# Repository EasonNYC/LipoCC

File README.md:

# LipoCC
Author: Eason Smith (Eason@EasonRobotics.com)

A Coulomb Counter PCB for LiPo battery monitoring. Designed in Cadsoft Eagle.

Further details can be found at [http://www.easonrobotics.com/?portfolio=lipocc](http://www.easonrobotics.com/?portfolio=lipocc)

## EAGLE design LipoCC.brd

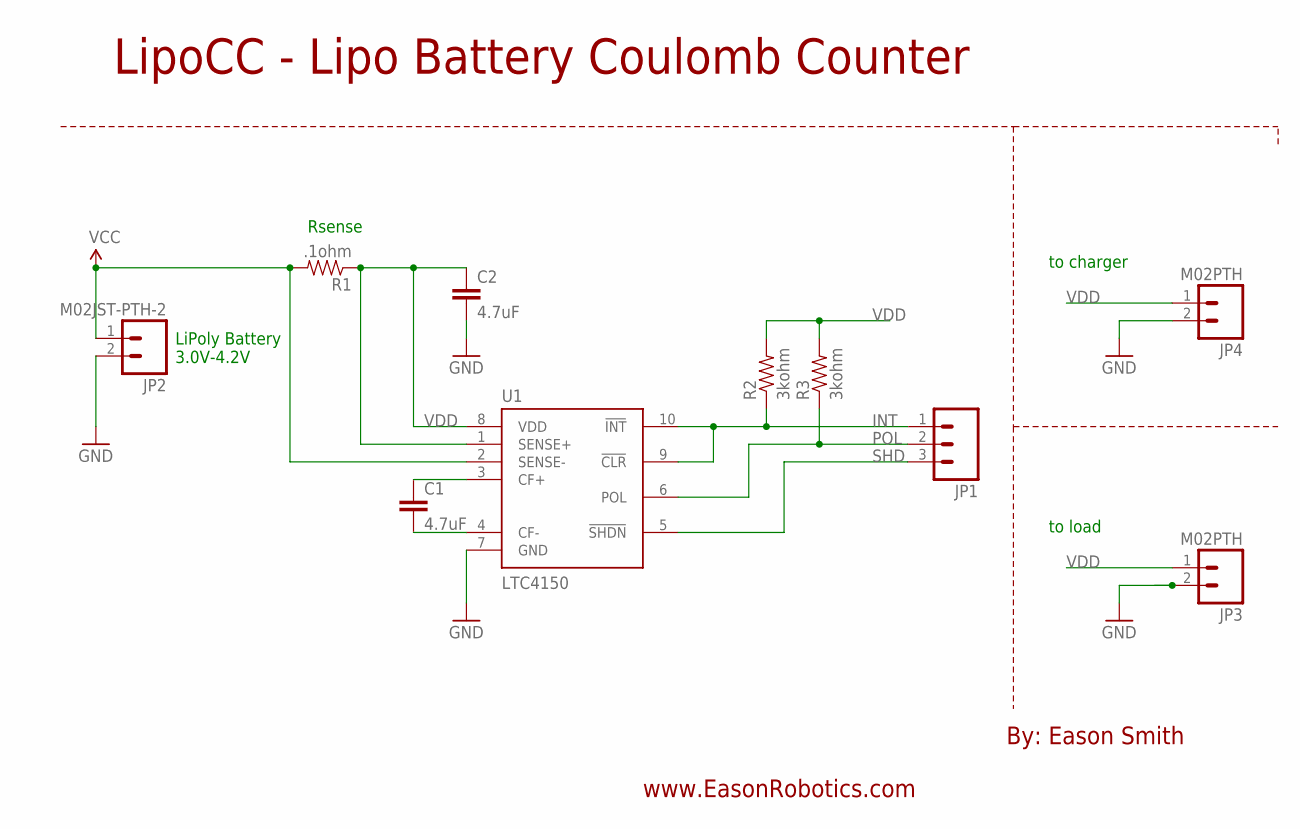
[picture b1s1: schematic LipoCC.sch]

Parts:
C1, C2: 4.7uF; 0603-CAP
JP1: M03PTH; 1X03
JP2: M02JST-PTH-2; JST-2-PTH
JP3, JP4: M02PTH; 1X02
R1: .1ohm; 0603-RES
R2, R3: 3kohm; 0603-RES
U1: LTC4150; MSOP10

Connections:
GND: C2.2, JP2.2, JP3.2, JP4.2, U1.7 (GND)
INT: JP1.1, R2.1, U1.9 (!CLR!), U1.10 (!INT!)
unnamed: C1.1, U1.3 (CF+)
unnamed: C1.2, U1.4 (CF-)
POL: JP1.2, R3.1, U1.6 (POL)
SHD: JP1.3, U1.5 (!SHDN!)
VCC: JP2.1, R1.2, U1.2 (SENSE-)
VDD: C2.1, JP3.1, JP4.1, R1.1, R2.2, R3.2, U1.1 (SENSE+), U1.8 (VDD)

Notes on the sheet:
Rsense
to charger
to load
LiPoly Battery 3.0V-4.2V
By: Eason Smith
LipoCC - Lipo Battery Coulomb Counter
www.EasonRobotics.com

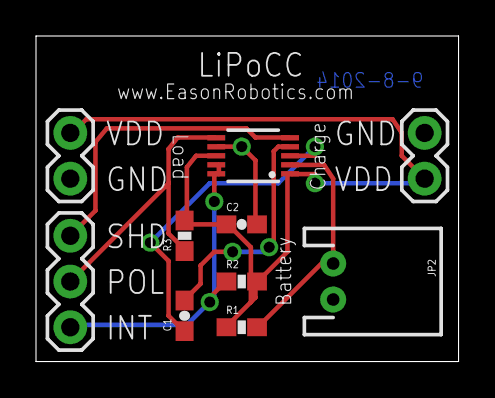
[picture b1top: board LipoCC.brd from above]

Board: 2 copper layers, 23.5 x 18.1 mm, 10 parts (0 on the bottom side), 8 nets.

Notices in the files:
parts and their libraries:
SparkFun-DigitalIC: Licensing: Creative Commons ShareAlike 4.0 International - https://creativecommons.org/licenses/by-sa/4.0
